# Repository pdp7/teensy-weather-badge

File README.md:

# teensy-weather-badge
Weather badge with Teensy 3.2 or LC, Adafruit 128x32 OLED (i2c) and Adafruit BME280 (i2c)

## Shared Project:
* [OSH Park: Ab57il2e](https://oshpark.com/shared_projects/Ab57il2e)

## Bill of Materials:
* [Adafruit I2C OLED (128x32)](https://www.adafruit.com/product/931)
* [Adafruit I2C BME280 (temp/hum/press)](https://www.adafruit.com/product/2652)
* Teensy:
   * Option 1: [Teensy 3.2 - OSH Park Edition](https://oshpark.com/teensy)
  * Option 2: [Teensy LC - OSH Park Edition](http://store.oshpark.com/products/teensy-lc)

## Photos:
* [instagram](https://www.instagram.com/p/BHsfERNAH9x/?taken-by=oshpark)
* [twitter](https://twitter.com/pdp7/status/762103242037886977)

## License
This project released under the CERN Open Hardware v1.2 License

**Note:** `teensy-weather-badge.ino` contains code written by Limor Fried & Kevin Townsend for Adafruit Industries and is covered by BSD license

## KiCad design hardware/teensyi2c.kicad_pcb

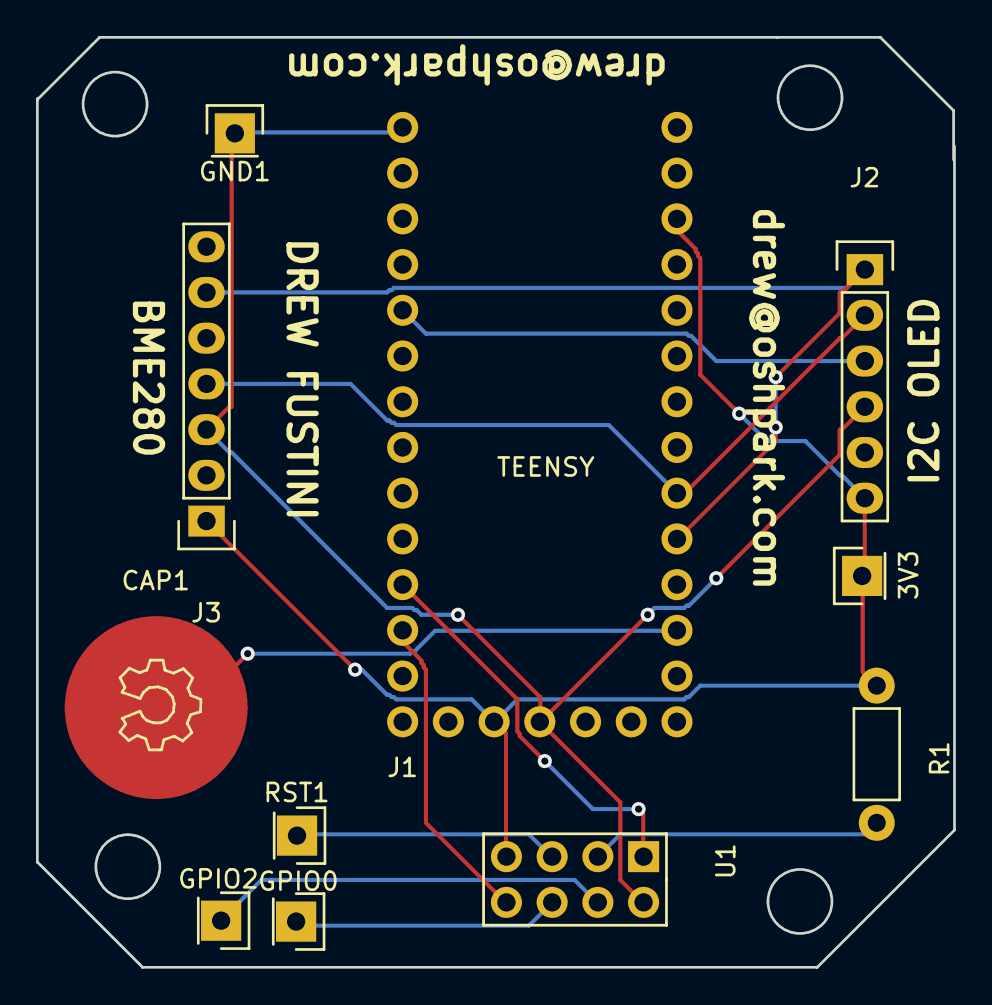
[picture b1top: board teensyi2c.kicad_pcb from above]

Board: 2 copper layers, 51.0 x 51.7 mm, 11 parts (0 on the bottom side), 12 nets.

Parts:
3V3: 3V3; Pin_Header_Straight_1x01
CAP1: CAPSENSE_CIRCLE; CAPSENSE_CIRCLE_D10
GND1: GND; Pin_Header_Straight_1x01
GPIO0: GPIO0; Pin_Header_Straight_1x01
GPIO2: GPIO2; Pin_Header_Straight_1x01
J1: TEENSY3.2-72MHz; TEENSY-LC
J2: OLED-I2C; Pin_Header_Straight_1x06
J3: ADAFRUIT_BME280; Pin_Header_Straight_1x07
R1: R; Resistor_Horizontal_RM7mm
RST1: RST; Pin_Header_Straight_1x01
U1: ESP-01v090; ESP-01

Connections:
/GND: GND1.1, J1.G1, J1.G2, J2.4, J3.3, U1.2
/RST: J1.3, J2.3
/SCK: J1.18, J2.2, J3.4
/SDA: J1.17, J2.1, J3.6
/VIN: 3V3.1, J1.3V1, J1.3V2, J2.6, J3.1, R1.1, U1.7
unnamed: CAP1.1, J1.15
unnamed: GPIO0.1, U1.6
unnamed: GPIO2.1, U1.4
unnamed: J1.9, U1.1
unnamed: J1.10, U1.8
unnamed: R1.2, U1.3
unnamed: RST1.1, U1.5

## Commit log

2016-07-09 Released under the CERN Open Hardware v1.2 License
2016-07-09 Add teensyi2c.kicad_pcb
    From https://oshpark.com/shared_projects/Ab57il2e
2016-07-28 add hardware schematic and layout
2016-07-28 update layout
2016-07-28 fix silkscreen
2016-07-28 fix gnd air wire
2016-08-05 fix i2c bus pins
2016-08-05 add commit and github url to silkscreen
2016-08-05 refill ground plane
